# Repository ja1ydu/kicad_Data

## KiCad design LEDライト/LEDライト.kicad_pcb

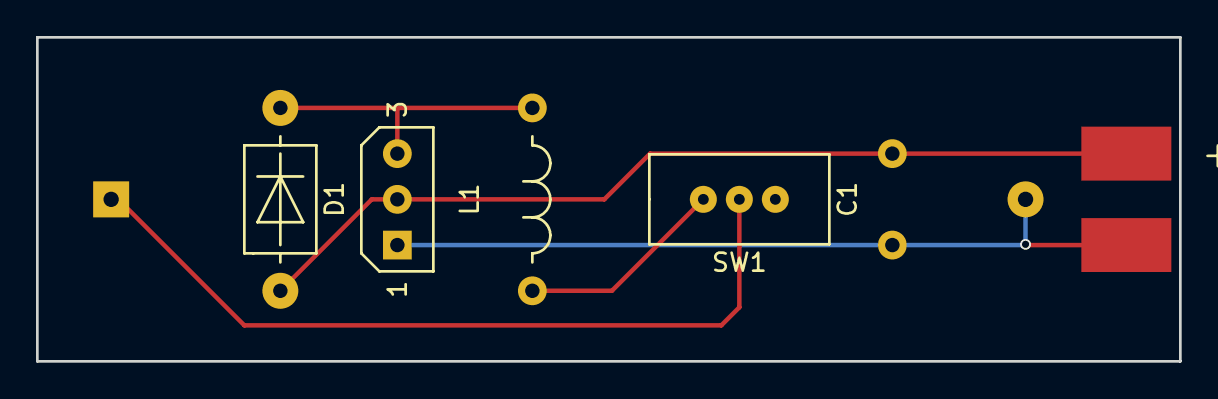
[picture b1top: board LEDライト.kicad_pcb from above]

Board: 2 copper layers, 63.5 x 18.0 mm, 7 parts (1 on the bottom side), 5 nets.

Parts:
BT1: Battery; battboxAAAx1
C1: C; CP
D1: D_Schottky; Diode
D2: LED
L1: L; COIL
SW1: SWITCH_INV; SWslide
U1: HT7733

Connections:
GND: BT1.2, C1.2, D2.1, U1.1
unnamed: BT1.1, SW1.2
unnamed: C1.1, D1.1, D2.2, U1.2
unnamed: D1.2, L1.1, U1.3
unnamed: L1.2, SW1.1

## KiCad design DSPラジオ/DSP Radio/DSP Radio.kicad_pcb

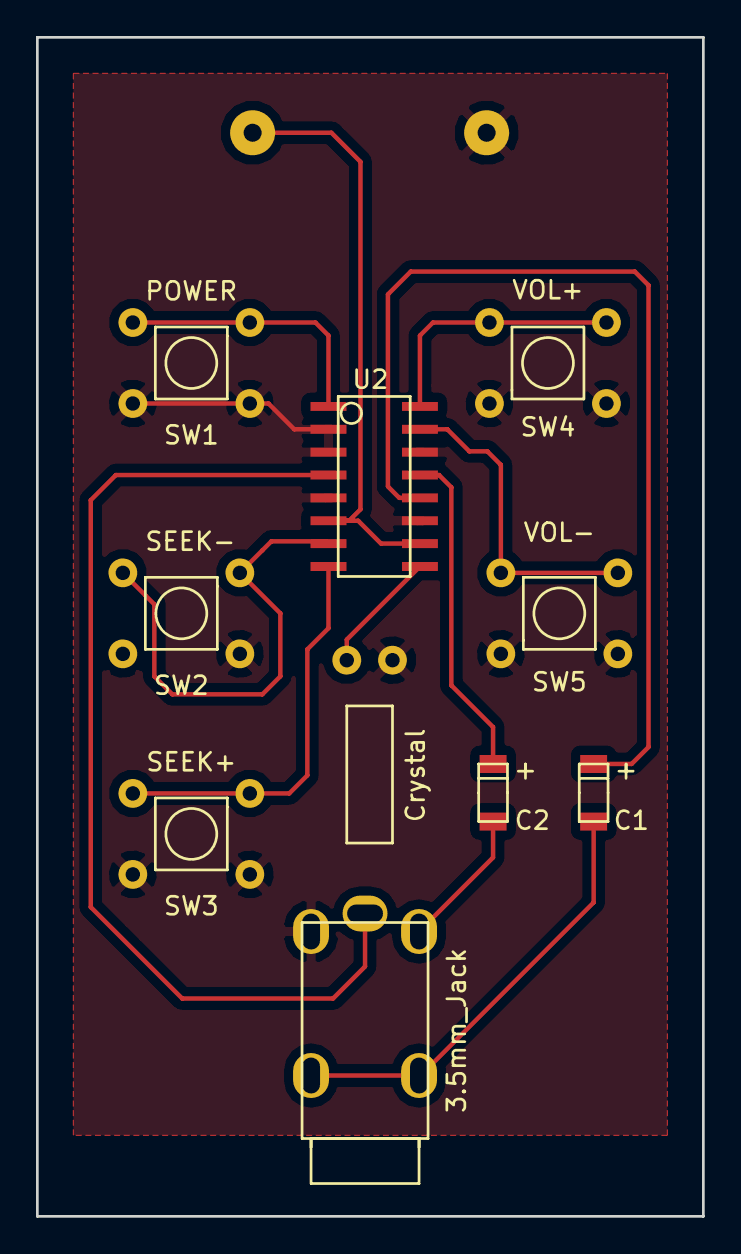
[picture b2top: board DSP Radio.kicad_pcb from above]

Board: 2 copper layers, 37.0 x 65.5 mm, 11 parts (1 on the bottom side), 13 nets.

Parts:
BT1: Battery; P-03086
C1, C2: 100u; 1206chipcapacitor
SW1: POWER; tactswitch
SW2: SEEK-; tactswitch
SW3: SEEK+; tactswitch
SW4: VOL+; tactswitch
SW5: VOL-; tactswitch
U1: 3.5mm_Jack; 3.5mmjack
U2: GS1299; SC1299
Y1: Crystal; crystal

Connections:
GND: BT1.2, SW1.1, SW2.1, SW3.1, SW4.2, SW5.2, U1.4, U2.2, U2.3, U2.5, U2.11, U2.14, Y1.2
unnamed: BT1.1, U2.6, U2.10
unnamed: C1.1, U2.12
unnamed: C1.2, U1.3
unnamed: C2.1, U2.13
unnamed: C2.2, U1.2
unnamed: SW1.2, U2.1
unnamed: SW2.2, U2.7
unnamed: SW3.2, U2.8
unnamed: SW4.1, U2.16
unnamed: SW5.1, U2.15
unnamed: U1.1, U2.4
unnamed: U2.9, Y1.1

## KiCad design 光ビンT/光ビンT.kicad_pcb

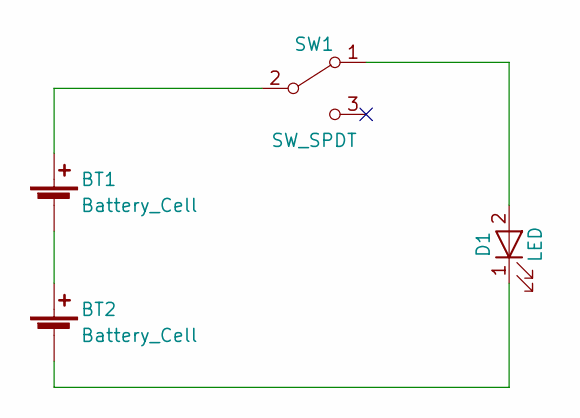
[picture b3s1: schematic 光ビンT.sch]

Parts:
BT1, BT2: Battery_Cell; LR44
D1: LED; LED_D5.0mm
SW1: SW_SPDT; SW_throughHole

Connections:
unnamed: BT1.1 (+), SW1.2 (B)
unnamed: BT1.2 (-), BT2.1 (+)
unnamed: BT2.2 (-), D1.1 (K)
unnamed: D1.2 (A), SW1.1 (A)

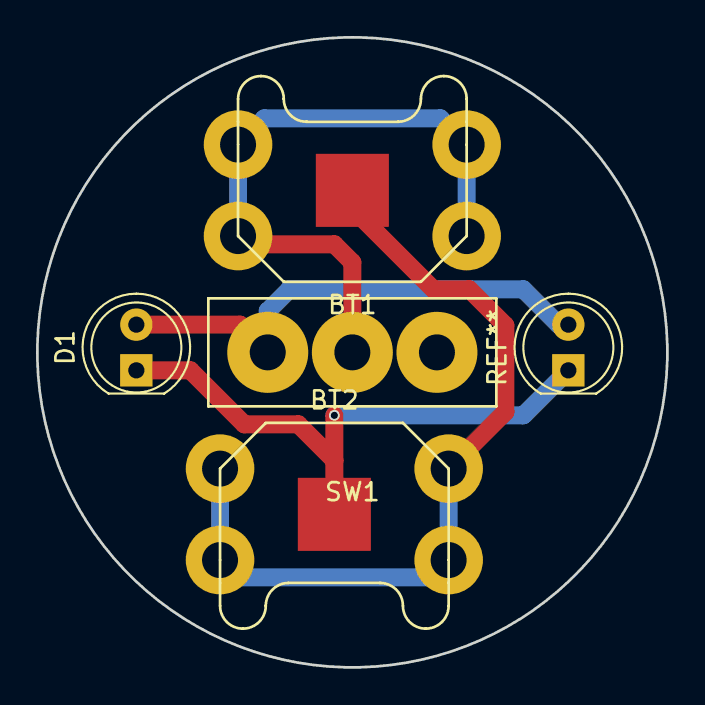
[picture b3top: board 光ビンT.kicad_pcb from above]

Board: 2 copper layers, 35.0 x 35.0 mm, 4 parts (0 on the bottom side), 4 nets.

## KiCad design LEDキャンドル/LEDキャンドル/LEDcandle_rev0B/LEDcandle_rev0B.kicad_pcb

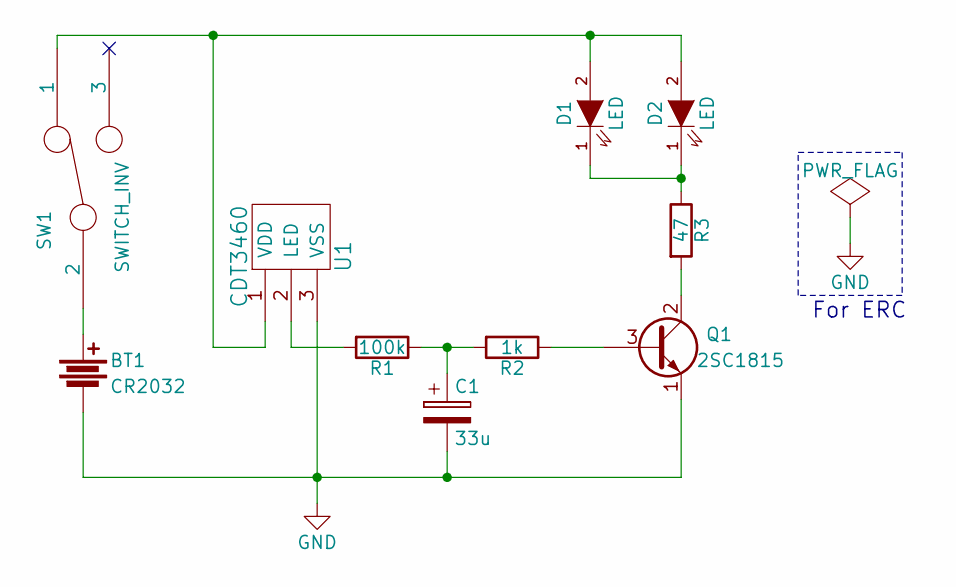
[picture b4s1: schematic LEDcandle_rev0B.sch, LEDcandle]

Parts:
BT1: CR2032; BS2032-C
C1: 33u; CP3mm
D1, D2: LED; LED3mm
Q1: 2SC1815; TO-92transistor
R1: 100k; Rdenkensize
R2: 1k; Rdenkensize
R3: 47; Rdenkensize
SW1: SWITCH_INV; SS12D07-NL
U1: CDT3460

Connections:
GND: BT1.2, C1.2, Q1.1 (E), U1.3 (VSS)
unnamed: BT1.1, SW1.2
unnamed: C1.1, R1.1, R2.2
unnamed: D1.1 (K), D2.1 (K), R3.1
unnamed: D1.2 (A), D2.2 (A), SW1.1, U1.1 (VDD)
unnamed: Q1.2 (C), R3.2
unnamed: Q1.3 (B), R2.1
unnamed: R1.2, U1.2 (LED)

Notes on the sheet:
For ERC

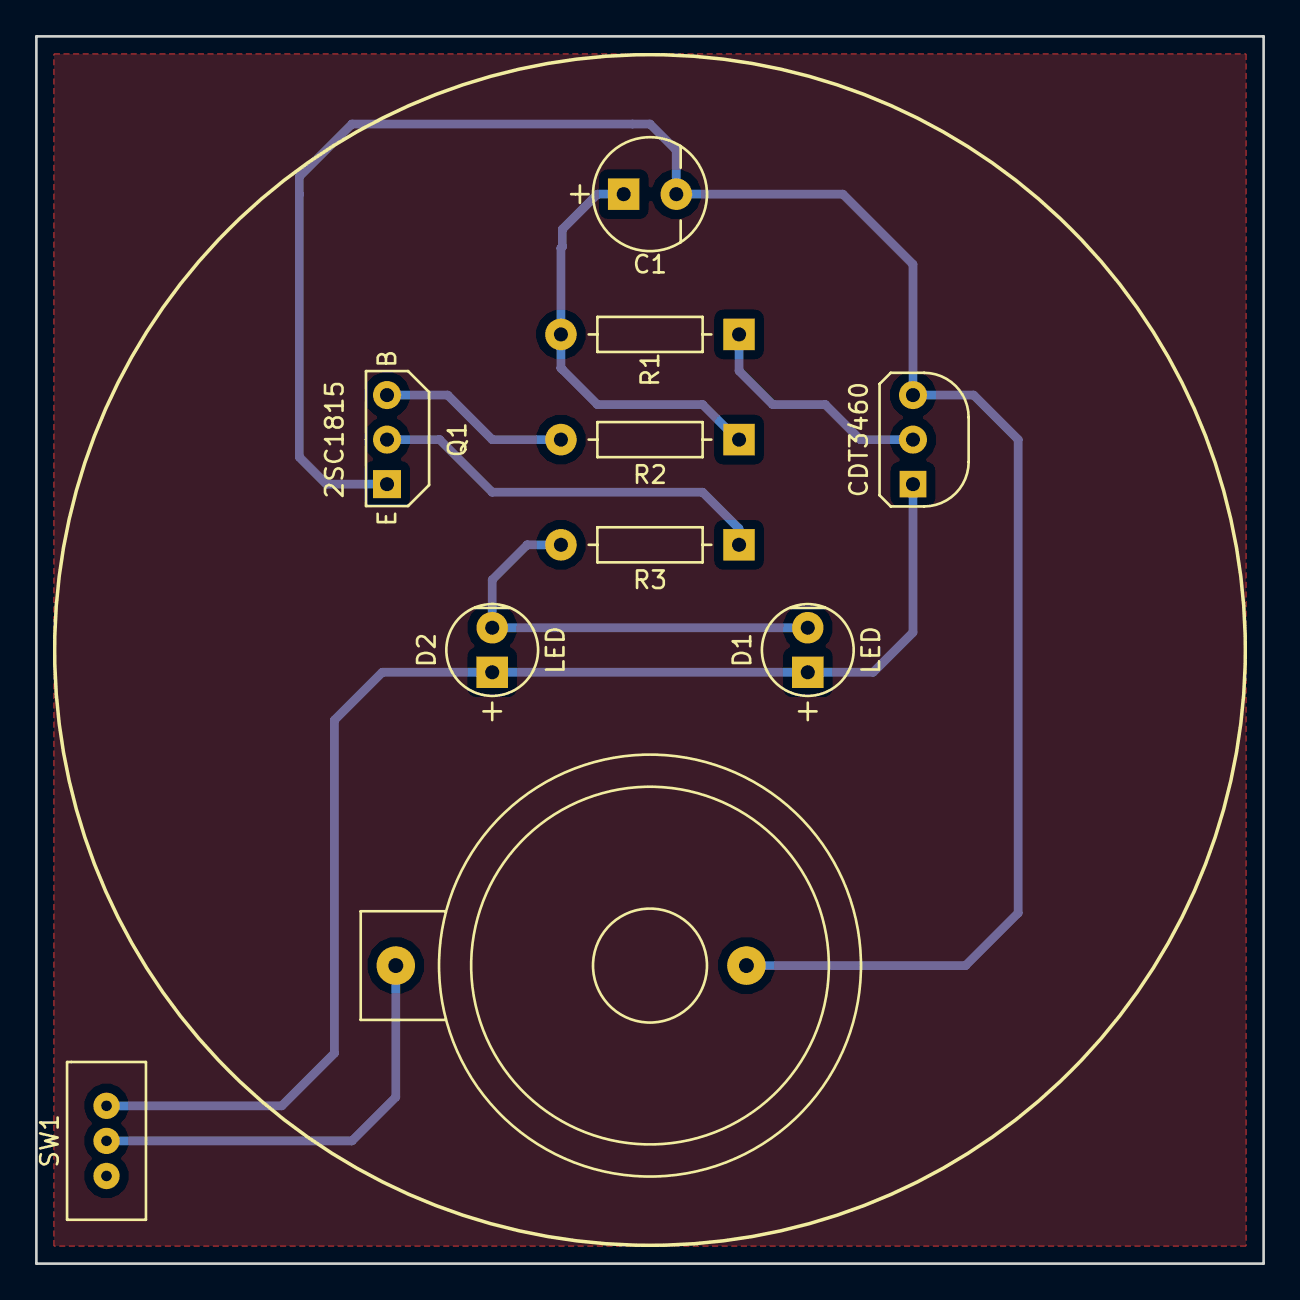
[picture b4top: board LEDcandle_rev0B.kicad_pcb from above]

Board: 2 copper layers, 70.0 x 70.0 mm, 10 parts (0 on the bottom side), 8 nets.

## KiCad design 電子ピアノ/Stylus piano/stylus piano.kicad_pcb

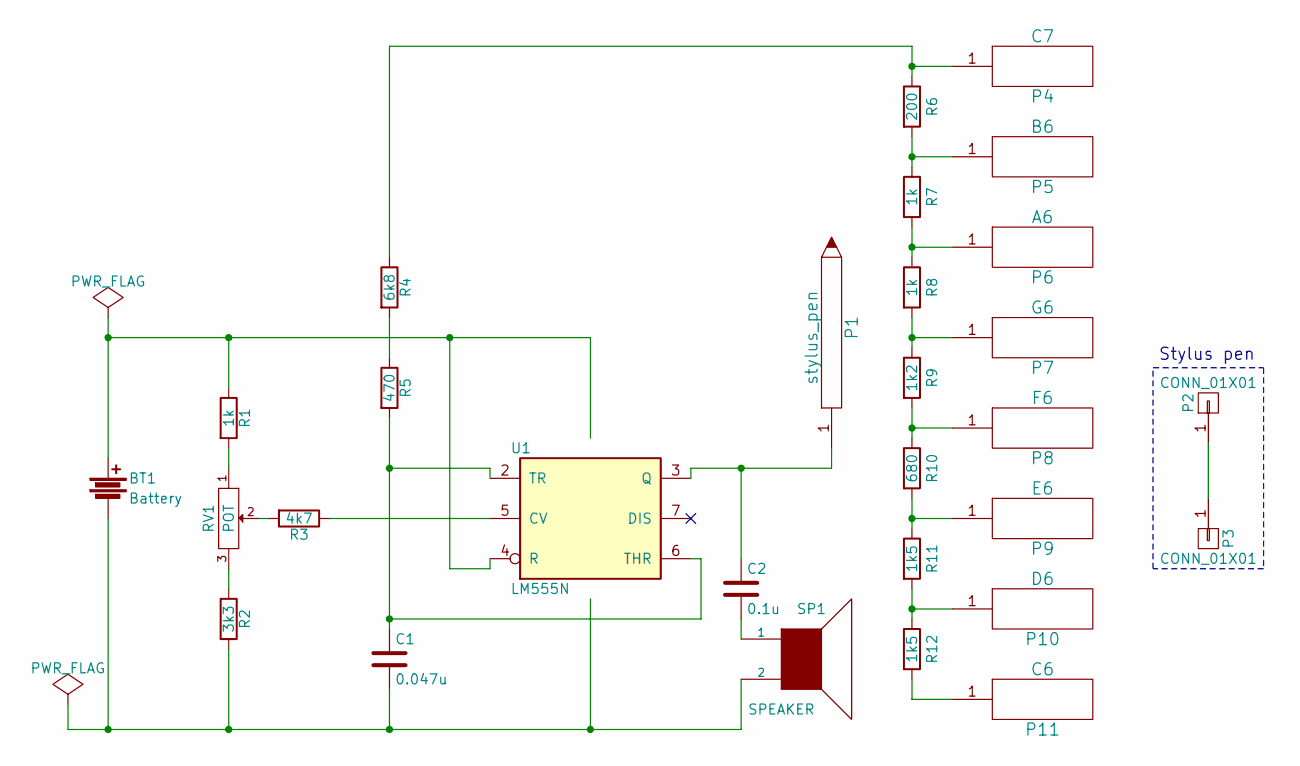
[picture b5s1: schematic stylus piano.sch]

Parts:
BT1: Battery; BH-321-1P24
C1: 0.047u; CP
C2: 0.1u; CP
P1: stylus_pen; holepin
P2, P3: CONN_01X01; holepin
P4: C7; keybord_1
P5: B6; keybord_1
P6: A6; keybord_1
P7: G6; keybord_1
P8: F6; keybord_1
P9: E6; keybord_1
P10: D6; keybord_1
P11: C6; keybord_1
R1, R7, R8: 1k; R_H_5
R2: 3k3; R_H_5
R3: 4k7; R_H_5
R4: 6k8; R_H_5
R5: 470; R_H_5
R6: 200; R_H_5
R9: 1k2; R_H_5
R10: 680; R_H_5
R11, R12: 1k5; R_H_5
RV1: POT; pod
SP1: SPEAKER; Speaker
U1: LM555N; DIP-8_W7.62mm_LongPads

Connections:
GND: BT1.2, C1.2, R2.2, SP1.2, U1.1 (GND)
unnamed: C1.1, R5.2, U1.2 (TR), U1.6 (THR)
unnamed: C2.1, P1.1, U1.3 (Q)
unnamed: C2.2, SP1.1
unnamed: P2.1, P3.1
unnamed: P4.1, R4.1, R6.1
unnamed: P5.1, R6.2, R7.1
unnamed: P6.1, R7.2, R8.1
unnamed: P7.1, R8.2, R9.1
unnamed: P8.1, R9.2, R10.1
unnamed: P9.1, R10.2, R11.1
unnamed: P10.1, R11.2, R12.1
unnamed: P11.1, R12.2
unnamed: R1.2, RV1.1
unnamed: R2.1, RV1.3
unnamed: R3.1, U1.5 (CV)
unnamed: R3.2, RV1.2
unnamed: R4.2, R5.1
VCC: BT1.1, R1.1, U1.4 (R), U1.8 (VCC)

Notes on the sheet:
Stylus pen

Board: 2 copper layers, 29 parts (0 on the bottom side), 19 nets, no tracks yet.

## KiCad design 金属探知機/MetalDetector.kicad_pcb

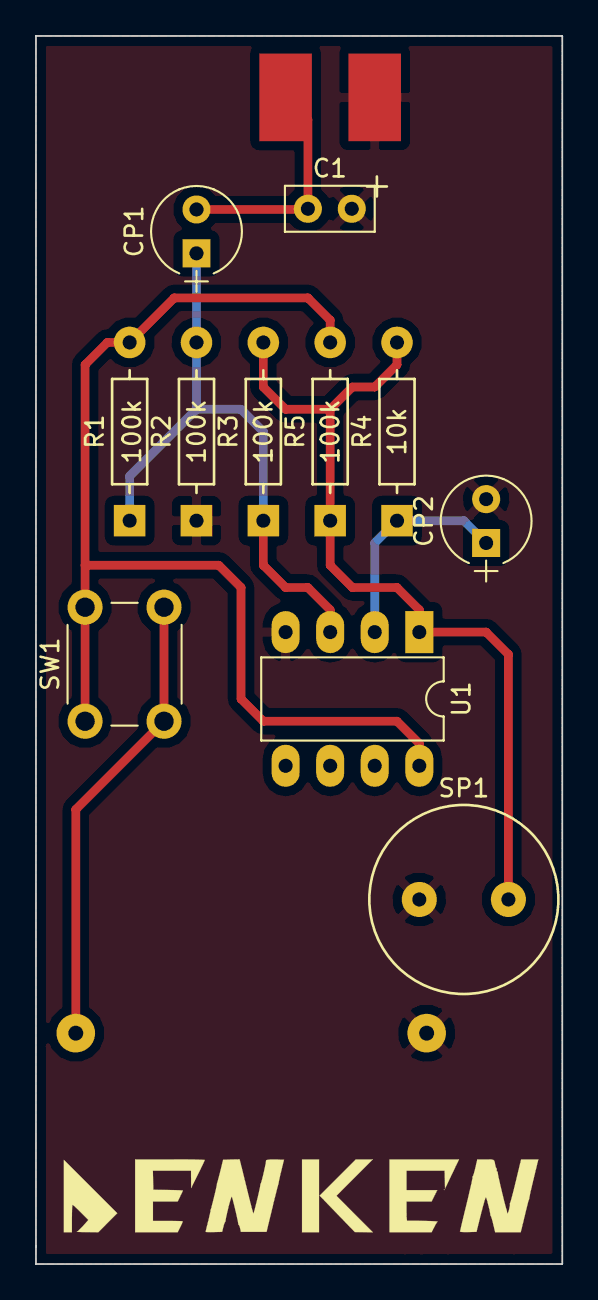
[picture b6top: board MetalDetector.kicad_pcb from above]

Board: 2 copper layers, 30.0 x 70.0 mm, 13 parts (1 on the bottom side), 7 nets.

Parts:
BT1: Battery; BS2032-C
C1: 4700p; C_Disc_D5.0mm_W2.5mm_P2.50mm
CP1: 10u; CP_Radial_Tantal_D5.0mm_P2.50mm
CP2: 4.7u; CP_Radial_Tantal_D5.0mm_P2.50mm
INDUCTOR1: 100uH; LED
R1, R2, R3, R5: 100k; Rdenkensize
R4: 10k; Rdenkensize
SP1: SPEAKER; Speaker
SW1: SW_PUSH; SW_PUSH_6mm_h13mm
U1: LM293; DIP-8_W7.62mm_LongPads

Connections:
+BATT: R1.1, R5.1, SW1.1, U1.8
GND: BT1.2, C1.2, CP2.2, INDUCTOR1.2, R2.2, SP1.2, U1.4
unnamed: BT1.1, SW1.2
unnamed: C1.1, CP1.2, INDUCTOR1.1
unnamed: CP1.1, R1.2, R2.1, R3.2, U1.3
unnamed: CP2.1, R4.2, U1.2
unnamed: R3.1, R4.1, R5.2, SP1.1, U1.1

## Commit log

2018-03-23 new files
